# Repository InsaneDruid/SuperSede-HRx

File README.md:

# SuperSede-HRx - a HRx clone family
A 100% compatible replica of the HR40, HR40B &amp; HR80 graphics boards for the CBM PET lineup.

The SuperSede HRx are 100% compatible clones of the HR40, HR40B and HR80 graphics boards for the PET/CBM series computers from 1982, beginning with the dynamic board.
They implements all the features, including the high 320*200 pixel high resolution graphics that can be mixed standard text output on a per character base, the availability of the 8k of onboard RAM for Data usage and the possibility to use existing ROM expansion on the graphics board.

## The HR40 board for the non CRTC 40column dynamic PET lineup

[Schematic](https://github.com/InsaneDruid/SuperSede-HRx/blob/main/hr40/hr40.pdf "Schematic")  

[Bill of Materials](https://htmlpreview.github.io/?https://github.com/InsaneDruid/SuperSede-HRx/blob/main/hr40/bom/hr40_bom.html "Bill of Materials")

[Wire connections](https://github.com/InsaneDruid/SuperSede-HRx/blob/main/hr40/hr40_connections.pdf "Wire connections" )

* The connection to the Character ROM can be made with a standard DIP24 to ribbon cable adapter.

* The connection to UF8 can be made with the provided breakout adapter found in [adapter_uf8](https://github.com/InsaneDruid/SuperSede-HRx/blob/main/adapter_uf8/ "adapter_uf8").

## The HR40b board for the CRTC based 40column PET/CBM lineup

[Schematic](https://github.com/InsaneDruid/SuperSede-HRx/blob/main/hr40b/hr40b.pdf "Schematic")  

[Bill of Materials](https://htmlpreview.github.io/?https://github.com/InsaneDruid/SuperSede-HRx/blob/main/hr40b/bom/hr40b_bom.html "Bill of Materials")

[Wire connections](https://github.com/InsaneDruid/SuperSede-HRx/blob/main/hr40b/hr40b_connections.pdf "Wire connections" )

* The connection to the CRTC can be made with the provided breakout adapter found in [adapter_crtc](https://github.com/InsaneDruid/SuperSede-HRx/blob/main/adapter_crtc/ "adapter_crtc").

## The HR80 board for the 80column CBM lineup (8032, 8032SK*, 8096)

[Schematic](https://github.com/InsaneDruid/SuperSede-HRx/blob/main/hr80/hr80.pdf "Schematic")  

[Bill of Materials](https://htmlpreview.github.io/?https://github.com/InsaneDruid/SuperSede-HRx/blob/main/hr80/bom/hr80_bom.html "Bill of Materials")

[Wire connections](https://github.com/InsaneDruid/SuperSede-HRx/blob/main/hr80/hr80_connections.pdf "Wire connections" )

* The connection to the CRTC can be made with the provided breakout adapter found in [adapter_crtc](https://github.com/InsaneDruid/SuperSede-HRx/blob/main/adapter_crtc/ "adapter_crtc").

## The SuperSede cards and Expansion ROMs
The SuperSede boards hav 8k of their own RAM which occupies memory locations 36864 to 45055 ($9000 to $AFFF). This is the Rom Expansion area, normally represented by sockets UD11 and UD12 (UD3 and UD4 for 9-inch PETs). 

When you power-up your computer the ROM sockets are enabled and the high resolution memory disabled. Thus Rom expansions can be used in standard text mode like normal.

## The Firmware
The firmware needed for the SuperSede cards consist of

* A modified CharRom (with inverted characters).
* A 4k ROM containing the EditorROM followed by the GRAPHIX software in the E900-EFFF area.

The Firmware and supporting tools are available on their own repository: [SuperSede-HRx-Software](https://github.com/InsaneDruid/SuperSede-HRx-Software/ "Firmware and tools for the SuperSede HRx boards ")

## The License
This work is licensed under a Creative Commons Attribution-ShareAlike 4.0 International License.   
See https://creativecommons.org/licenses/by-sa/4.0/.

## The Credits
This work would not have been possible without the help from a bunch of amazing people from [VzEkC e. V. forums](https://forum.classic-computing.de/forum/ "forum.classic-computing.de"). Many thanks go out to:

* *Andy Grady* - for the scans of a blank board that formed the backbone for this project, the construction of the first prototypes as well as writing the print routines and assembling the firmware for the cards.
* *Steve Gray* - for collecting a ton of information about the cards
* *CBM_Ba* and *Richy* - for prototyping, testing, feedback and general positive retrocomputing craziness

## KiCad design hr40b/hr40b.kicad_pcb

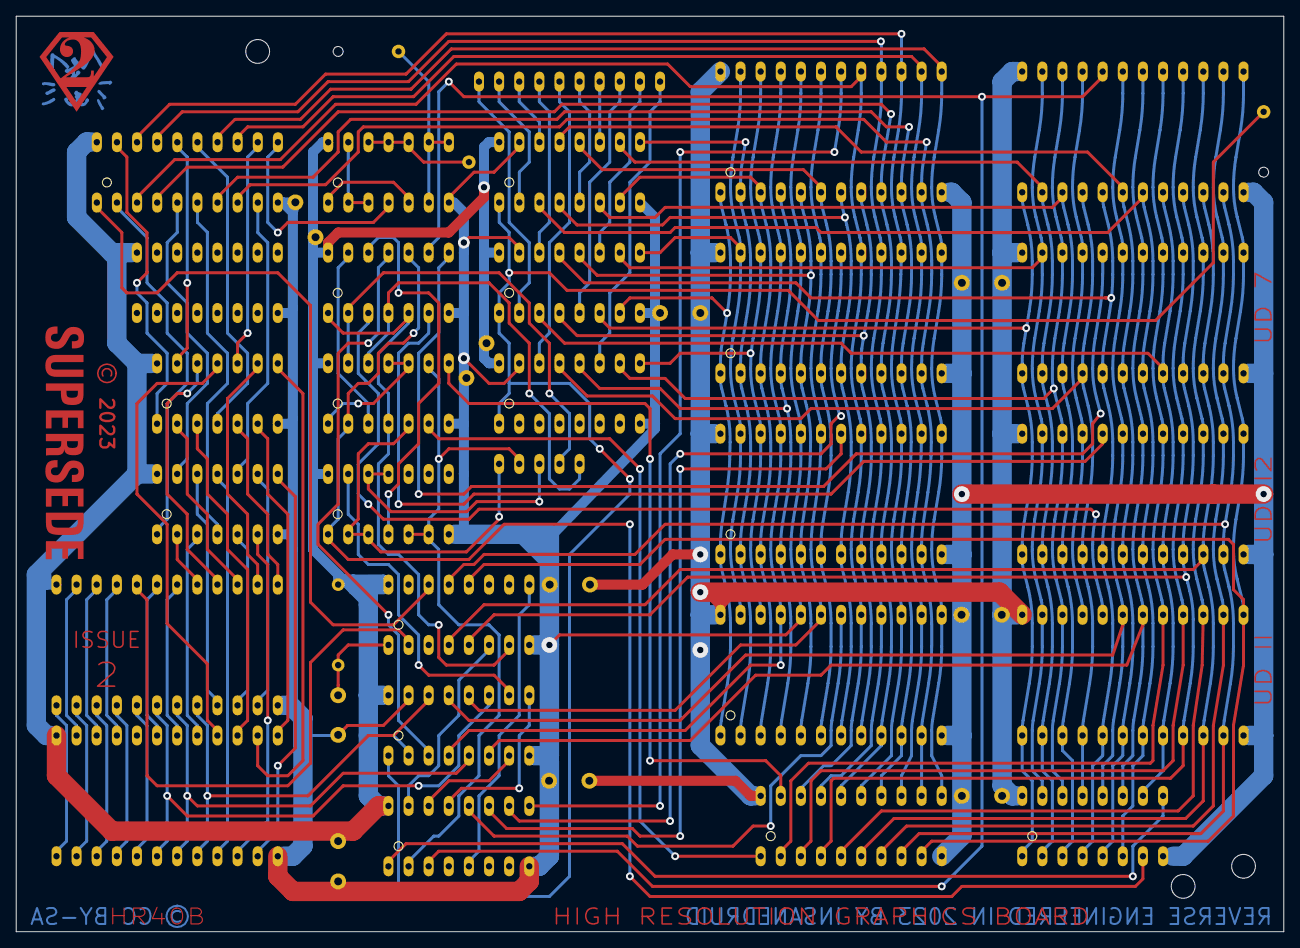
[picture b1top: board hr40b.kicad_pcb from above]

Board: 2 copper layers, 160.0 x 115.6 mm, 47 parts (0 on the bottom side), 128 nets.

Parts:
C1: 2.2uF; CP_Radial_D10.0mm_P5.00mm
C2, C3, C4, C5, C6, C7, C8, C9, C10: 100nF; C_Disc_D7.5mm_W2.5mm_P5.08mm
H1: CLK1; PinHeader_1x01_P2.54mm_Vertical
H2: VIDEO_LATCH; PinHeader_1x01_P2.54mm_Vertical
J0: charROM ADAPTER; DIP-24_W15.24mm_Adapter
J1: editorROM ADAPTER; DIP-24_W15.24mm_Adapter
J2: PET CRTC; PinHeader_1x10_P2.54mm_Vertical
J3: PET J4 / J9; PinHeader_1x05_P2.54mm_Vertical
MH0, MH5: MountingHole_3mm
MH2: MountingHole_1.25mm
Mh4: MountingHole_3mm
R1: 47k; R_Axial_DIN0207_L6.3mm_D2.5mm_P10.16mm_Horizontal
RMH1: MountingHole_1.25mm
TP1: MountingHole_Pad; PinHeader_1x01_P2.54mm_Vertical
U1: 74LS373; DIP-20_W7.62mm_LongPads
U2: 74LS157; DIP-16_W7.62mm_LongPads_Empty
U3, U4, U9: 74LS00; DIP-14_W7.62mm_LongPads
U5: 2316; DIP-24_W15.24mm_Socket_LongPads
U7, U10: 74LS02; DIP-14_W7.62mm_LongPads
U8: 74LS32; DIP-14_W7.62mm_LongPads
U11: 74LS175; DIP-16_W7.62mm_LongPads
U12, U14, U15, U16: 74LS157; DIP-16_W7.62mm_LongPads
U13: 74LS139; DIP-16_W7.62mm_LongPads
U17, U18, U19, U20: 6116; DIP-24_W15.24mm_LongPads
U21: 74LS245; DIP-20_W7.62mm_LongPads
U26: 74LS133; DIP-16_W7.62mm_LongPads
UD7: 2316; DIP-24_W15.24mm_Socket_LongPads
UD11, UD12: 2332A; DIP-24_W15.24mm_Socket_LongPads

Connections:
+5V: C2.1, C3.1, C4.1, J0.24 (VCC), R1.1, U1.20 (VCC), U2.16 (VCC), U3.14 (VCC), U4.14 (VCC), U5.24 (VCC), U7.14 (VCC), U8.14 (VCC), U9.14 (VCC), U10.14 (VCC), U11.16 (VCC), U12.2 (I0a), U12.16 (VCC), U13.16 (VCC), U14.16 (VCC), U15.16 (VCC), U16.16 (VCC)
+5VA: C5.1, C6.1, C7.1, C8.1, C9.1, C10.1, J1.24 (VCC), U17.24 (VCC), U18.24 (VCC), U19.24 (VCC), U20.24 (VCC), U21.20 (VCC), U26.16 (VCC), UD7.24 (VCC), UD11.24 (VCC), UD12.24 (VCC)
/A_{CHAR}0: J0.8 (A0), U5.8 (A0), U12.14 (I0d)
/A_{CHAR}1: J0.7 (A1), U5.7 (A1), U12.5 (I0b)
/A_{CHAR}2: J0.6 (A2), U5.6 (A2), U12.11 (I0c)
/A_{CHAR}3: J0.5 (A3), U5.5 (A3)
/A_{CHAR}4: J0.4 (A4), U5.4 (A4)
/A_{CHAR}5: J0.3 (A5), U5.3 (A5)
/A_{CHAR}6: J0.2 (A6), U5.2 (A6)
/A_{CHAR}7: J0.1 (A7), U5.1 (A7)
/A_{CHAR}8: J0.23 (A8), U5.23 (A8)
/A_{CHAR}9: J0.22 (A9), U5.22 (A9)
/A_{CHAR}10: J0.19 (A10), U5.19 (A10)
/A_{CHAR}11: J0.18 (~CS2), U5.18 (~CS2)
/A_{PET}0: J1.8 (A0), U15.3 (I1a), U26.10, UD7.8 (A0), UD11.8 (A0), UD12.8 (A0)
/A_{PET}1: J1.7 (A1), U14.3 (I1a), U26.6, UD7.7 (A1), UD11.7 (A1), UD12.7 (A1)
/A_{PET}2: J1.6 (A2), U14.13 (I1d), U26.5, UD7.6 (A2), UD11.6 (A2), UD12.6 (A2)
/A_{PET}3: J1.5 (A3), U15.13 (I1d), U26.4, UD7.5 (A3), UD11.5 (A3), UD12.5 (A3)
/A_{PET}4: J1.4 (A4), U16.13 (I1d), U26.13, UD7.4 (A4), UD11.4 (A4), UD12.4 (A4)
/A_{PET}5: J1.3 (A5), U14.6 (I1b), U26.3, UD7.3 (A5), UD11.3 (A5), UD12.3 (A5)
/A_{PET}6: J1.2 (A6), U14.10 (I1c), U26.2, UD7.2 (A6), UD11.2 (A6), UD12.2 (A6)
/A_{PET}7: J1.1 (A7), U15.6 (I1b), U26.1, UD7.1 (A7), UD11.1 (A7), UD12.1 (A7)
/A_{PET}8: J1.23 (A8), U15.10 (I1c), U26.15, UD7.23 (A8), UD11.23 (A8), UD12.23 (A8)
/A_{PET}9: J1.22 (A9), U16.10 (I1c), U26.14, UD7.22 (A9), UD11.22 (A9), UD12.22 (A9)
/A_{RAM}0: U15.4 (Za), U17.8 (A0), U18.8 (A0), U19.8 (A0), U20.8 (A0)
/A_{RAM}1: U14.4 (Za), U17.7 (A1), U18.7 (A1), U19.7 (A1), U20.7 (A1)
/A_{RAM}2: U14.12 (Zd), U17.6 (A2), U18.6 (A2), U19.6 (A2), U20.6 (A2)
/A_{RAM}3: U15.12 (Zd), U17.5 (A3), U18.5 (A3), U19.5 (A3), U20.5 (A3)
/A_{RAM}4: U16.12 (Zd), U17.4 (A4), U18.4 (A4), U19.4 (A4), U20.4 (A4)
/A_{RAM}5: U14.7 (Zb), U17.3 (A5), U18.3 (A5), U19.3 (A5), U20.3 (A5)
/A_{RAM}6: U14.9 (Zc), U17.2 (A6), U18.2 (A6), U19.2 (A6), U20.2 (A6)
/A_{RAM}7: U15.7 (Zb), U17.1 (A7), U18.1 (A7), U19.1 (A7), U20.1 (A7)
/A_{RAM}8: U15.9 (Zc), U17.23 (A8), U18.23 (A8), U19.23 (A8), U20.23 (A8)
/A_{RAM}9: U16.9 (Zc), U17.22 (A9), U18.22 (A9), U19.22 (A9), U20.22 (A9)
/A_{RAM}10: U12.12 (Zd), U17.19 (A10), U18.19 (A10), U19.19 (A10), U20.19 (A10)
/BA12: J3.3, U10.11, U10.12
/BR/W: J3.1, U9.5, U10.2, U10.3
/CS1_{PET}: J1.21 (~CS3), UD7.21 (~CS3), UD11.21 (CS1), UD12.21 (CS1)
/D_{CHAR}0: U4.12, U5.9 (D0)
/D_{CHAR}1: U4.5, U5.10 (D1)
/D_{CHAR}2: U4.9, U5.11 (D2)
/D_{CHAR}3: U3.5, U5.13 (D3)
/D_{CHAR}4: U3.9, U5.14 (D4)
/D_{CHAR}5: U3.2, U5.15 (D5)
/D_{CHAR}6: U3.12, U5.16 (D6)
/D_{CHAR}7: U4.2, U5.17 (D7)
/D_{OUT}0: U1.5 (O1), U4.13
/D_{OUT}1: U1.6 (O2), U4.4
/D_{OUT}2: U1.9 (O3), U4.10
/D_{OUT}3: U1.15 (O5), U3.4
/D_{OUT}4: U1.12 (O4), U3.10
/D_{OUT}5: U1.19 (O7), U3.1
/D_{OUT}6: U1.16 (O6), U3.13
/D_{OUT}7: U1.2 (O0), U4.1
/D_{PET}0: J1.9 (D0), U11.5 (D1), U21.4 (A2), UD7.9 (D0), UD11.9 (D0), UD12.9 (D0)
/D_{PET}1: J1.10 (D1), U11.4 (D0), U21.6 (A4), UD7.10 (D1), UD11.10 (D1), UD12.10 (D1)
/D_{PET}2: J1.11 (D2), U11.13 (D3), U21.8 (A6), UD7.11 (D2), UD11.11 (D2), UD12.11 (D2)
/D_{PET}3: J1.13 (D3), U11.12 (D2), U21.9 (A7), UD7.13 (D3), UD11.13 (D3), UD12.13 (D3)
/D_{PET}4: J1.14 (D4), U21.7 (A5), UD7.14 (D4), UD11.14 (D4), UD12.14 (D4)
/D_{PET}5: J1.15 (D5), U21.5 (A3), UD7.15 (D5), UD11.15 (D5), UD12.15 (D5)
/D_{PET}6: J1.16 (D6), U21.3 (A1), UD7.16 (D6), UD11.16 (D6), UD12.16 (D6)
/D_{PET}7: J1.17 (D7), U21.2 (A0), UD7.17 (D7), UD11.17 (D7), UD12.17 (D7)
/D_{RAM}0: U1.4 (D1), U17.9 (D0), U18.9 (D0), U19.9 (D0), U20.9 (D0), U21.16 (B2)
/D_{RAM}1: U1.7 (D2), U17.10 (D1), U18.10 (D1), U19.10 (D1), U20.10 (D1), U21.14 (B4)
/D_{RAM}2: U1.8 (D3), U17.11 (D2), U18.11 (D2), U19.11 (D2), U20.11 (D2), U21.12 (B6)
/D_{RAM}3: U1.14 (D5), U17.13 (D3), U18.13 (D3), U19.13 (D3), U20.13 (D3), U21.11 (B7)
/D_{RAM}4: U1.13 (D4), U17.14 (D4), U18.14 (D4), U19.14 (D4), U20.14 (D4), U21.13 (B5)
/D_{RAM}5: U1.18 (D7), U17.15 (D5), U18.15 (D5), U19.15 (D5), U20.15 (D5), U21.15 (B3)
/D_{RAM}6: U1.17 (D6), U17.16 (D6), U18.16 (D6), U19.16 (D6), U20.16 (D6), U21.17 (B1)
/D_{RAM}7: U1.3 (D0), U17.17 (D7), U18.17 (D7), U19.17 (D7), U20.17 (D7), U21.18 (B0)
/D_{VIDEO}0: J0.9 (D0), U4.11
/D_{VIDEO}1: J0.10 (D1), U4.6
/D_{VIDEO}2: J0.11 (D2), U4.8
/D_{VIDEO}3: J0.13 (D3), U3.6
/D_{VIDEO}4: J0.14 (D4), U3.8
/D_{VIDEO}5: J0.15 (D5), U3.3
/D_{VIDEO}6: J0.16 (D6), U3.11
/D_{VIDEO}7: J0.17 (D7), U4.3
/PHI2: J3.2, U9.9, U10.5, U10.6, U13.2 (A0)
/PULSE_VIDEO_LATCH: U1.11 (LE), U7.4
/TA0: J2.1, U15.2 (I0a)
/TA1: J2.2, U14.2 (I0a)
/TA2: J2.3, U14.14 (I0d)
/TA3: J2.4, U15.14 (I0d)
/TA4: J2.5, U16.14 (I0d)
/TA5: J2.6, U14.5 (I0b)
/TA6: J2.7, U14.11 (I0c)
/TA7: J2.8, U15.5 (I0b)
/TA8: J2.9, U15.11 (I0c)
/TA9: J2.10, U16.11 (I0c)
/VIDEO_LATCH: H2.1, U7.6, U7.8, U7.9
/~CS3_{CHAR}: J0.21 (~CS3), U5.21 (~CS3)
/~SEL9: J3.5, U8.4, U9.12
/~SELA: J3.4, U8.2, U9.13
/~WE: U8.11, U12.3 (I1a)
A_{PET}10: J1.19 (A10), U12.13 (I1d), U26.12, UD7.19 (A10), UD11.19 (A10), UD12.19 (A10)
A_{PET}11: J1.18 (~CS2), U12.6 (I1b), U26.11, UD7.18 (~CS2), UD11.18 (A11), UD12.18 (A11)
CLK1: H1.1, U12.1 (S), U14.1 (S), U15.1 (S), U16.1 (S)
CS_{PETtoRAM}: U9.8, U21.19 (CE)
GND: C1.2, C2.2, C3.2, C4.2, C5.2, C6.2, C7.2, J0.12 (GND), U1.10 (GND), U2.8 (GND), U3.7 (GND), U4.7 (GND), U5.12 (GND), U7.7 (GND), U8.7 (GND), U9.7 (GND), U10.7 (GND), U11.8 (GND), U12.8 (GND), U12.15 (E), U13.8 (GND), U14.8 (GND), U14.15 (E), U15.8 (GND), U15.15 (E), U16.8 (GND), U16.15 (E), U17.20 (~OE), U18.20 (~OE), U19.20 (~OE), U20.20 (~OE)
GNDA: C8.2, C9.2, C10.2, J1.12 (GND), U17.12 (GND), U18.12 (GND), U19.12 (GND), U20.12 (GND), U21.10 (GND), U26.8 (GND), UD7.12 (GND), UD11.12 (GND), UD12.12 (GND)
unnamed: TP1.1, U7.10, U7.11, U7.12
unnamed: U7.1, U7.5
unnamed: U7.2, U7.3, U7.13
unnamed: U9.1, U9.10, U9.11
unnamed: U11.9 (Cp), U13.5 (O1)
unnamed: U8.1, U8.5, U9.4, U11.7 (Q1)
unnamed: C1.1, R1.2, U11.1 (~Mr)
unnamed: U11.6 (~Q1), U13.15 (E)
unnamed: U10.13, U12.10 (I1c)
unnamed: U12.7 (Zb), U13.14 (A0)
unnamed: U12.9 (Zc), U13.13 (A1)
OE_{LATCH_RAM}: U1.1 (OE), U11.14 (~Q3)
SWITCH_{PETtoRAM}: U9.6, U21.1 (A->B)
WEa: U8.12, U10.4
WEb: U8.13, U9.3
~ADDR: U13.1 (E), U26.9
~BR_W: U8.10, U9.2, U10.1, U26.7
~CS1_CHAR: U5.20 (~CS1), U11.2 (Q0)
~CS_{RAM1}: U13.9 (O3), U17.18 (~CS)
~CS_{RAM2}: U13.10 (O2), U18.18 (~CS)
~CS_{RAM3}: U13.11 (O1), U19.18 (~CS)
~CS_{RAM4}: U13.12 (O0), U20.18 (~CS)
~SEL9_{A}: U8.6, UD12.20 (~CS2)
~SELA_{A}: U8.3, UD11.20 (~CS2)
~SELE: J1.20 (~CS1), U8.9, U13.3 (A1)
~SELE_{A}: U8.8, UD7.20 (~CS1)
~WE_{RAM}: U12.4 (Za), U17.21 (~WE), U18.21 (~WE), U19.21 (~WE), U20.21 (~WE)

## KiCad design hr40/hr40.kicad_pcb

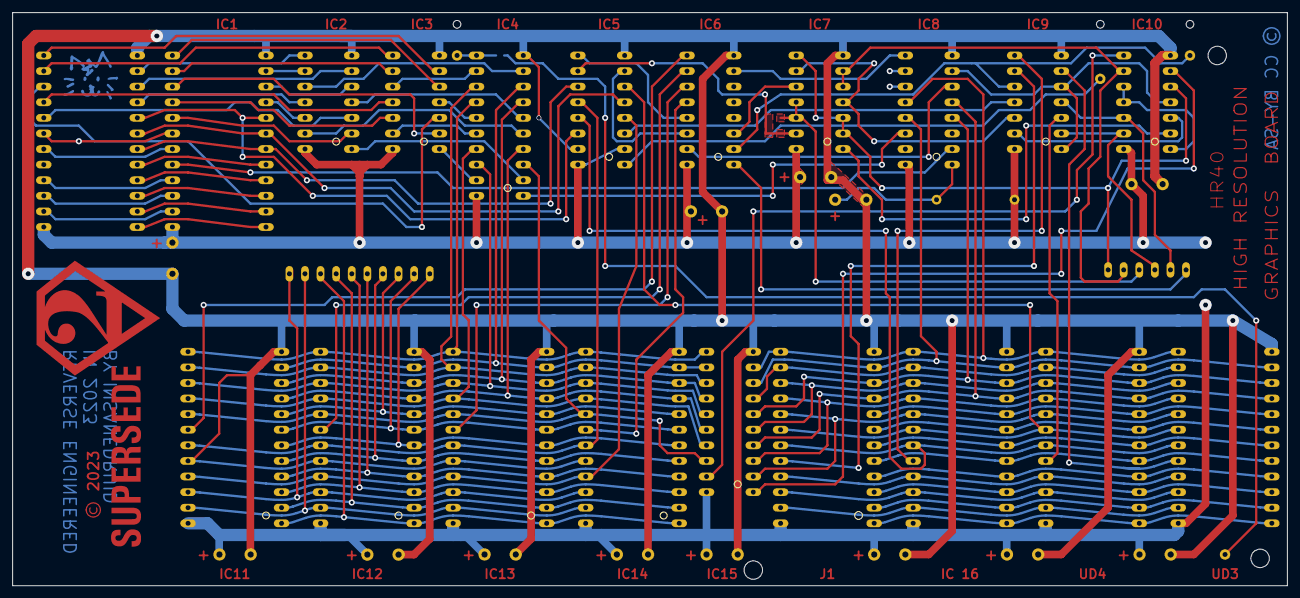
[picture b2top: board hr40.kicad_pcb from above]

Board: 2 copper layers, 207.6 x 93.3 mm, 47 parts (1 on the bottom side), 116 nets.

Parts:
C2, C3, C4, C5, C6, C7, C9, C10, C11, C12, C13, C14: 100nF; C_Disc_D7.5mm_W2.5mm_P5.08mm
C8: 2.2uF; C_Disc_D7.5mm_W2.5mm_P5.08mm
H1: CLK1; PinHeader_1x01_P2.54mm_Vertical
H2, H4: VIDEO_LATCH; PinHeader_1x01_P2.54mm_Vertical
H3: X8XX; PinHeader_1x01_P2.54mm_Vertical
IC1: 2316; DIP-24_W15.24mm_Socket_LongPads
IC2, IC3, IC10: 74LS00; DIP-14_W7.62mm_LongPads
IC4: 74LS373; DIP-20_W7.62mm_LongPads
IC5: 74LS157; DIP-16_W7.62mm_LongPads
IC6: 74LS139; DIP-16_W7.62mm_LongPads
IC7: 74LS02; DIP-14_W7.62mm_LongPads
IC8: 74LS175; DIP-16_W7.62mm_LongPads
IC9: 74LS32; DIP-14_W7.62mm_LongPads
IC11, IC12, IC13, IC14: 6116; DIP-24_W15.24mm_LongPads
IC16: 2332A; DIP-24_W15.24mm_Socket_LongPads
J0: charROM ADAPTER; DIP-24_W15.24mm_Adapter
J1: editorROM ADAPTER; DIP-24_W15.24mm_WireAdapter
J2: PET F8; PinHeader_1x10_P2.54mm_Vertical
J3: PET J4 / J9; PinHeader_1x06_P2.54mm_Vertical
JP1: Jumper_2_Open; SolderJumper-2_P1.3mm_Open_RoundedPad1.0x1.5mm
MH0, MH1, MH2: MountingHole_1.25mm
MH3, MH4, MH5: MountingHole_3mm
R1: 47k; R_Axial_DIN0207_L6.3mm_D2.5mm_P12.70mm_Horizontal
U21: 74LS245; DIP-20_W7.62mm_LongPads
UD3, UD4: 2332A; DIP-24_W15.24mm_Socket_LongPads

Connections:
+5V: C2.1, C4.1, C6.1, C7.1, IC1.24 (VCC), IC2.14 (VCC), IC3.14 (VCC), IC4.20 (VCC), IC5.2 (I0a), IC5.16 (VCC), IC6.16 (VCC), IC7.14 (VCC), IC8.16 (VCC), IC9.14 (VCC), IC10.14 (VCC), J0.24 (VCC), R1.1
+5VA: C3.1, C5.1, C9.1, C10.1, C11.1, C12.1, C13.1, C14.1, IC11.24 (VCC), IC12.24 (VCC), IC13.24 (VCC), IC14.24 (VCC), IC16.24 (VCC), J1.24 (VCC), U21.20 (VCC), UD3.24 (VCC), UD4.24 (VCC)
/A_{CHAR}0: IC1.8 (A0), IC5.14 (I0d), J0.8 (A0)
/A_{CHAR}1: IC1.7 (A1), IC5.5 (I0b), J0.7 (A1)
/A_{CHAR}2: IC1.6 (A2), IC5.11 (I0c), J0.6 (A2)
/A_{CHAR}3: IC1.5 (A3), J0.5 (A3)
/A_{CHAR}4: IC1.4 (A4), J0.4 (A4)
/A_{CHAR}5: IC1.3 (A5), J0.3 (A5)
/A_{CHAR}6: IC1.2 (A6), J0.2 (A6)
/A_{CHAR}7: IC1.1 (A7), J0.1 (A7)
/A_{CHAR}8: IC1.23 (A8), J0.23 (A8)
/A_{CHAR}9: IC1.22 (A9), J0.22 (A9)
/A_{CHAR}10: IC1.19 (A10), J0.19 (A10)
/A_{CHAR}11: IC1.18 (~CS2), J0.18 (~CS2)
/A_{PET}0: IC16.8 (A0), J1.8 (A0), UD3.8 (A0), UD4.8 (A0)
/A_{PET}1: IC16.7 (A1), J1.7 (A1), UD3.7 (A1), UD4.7 (A1)
/A_{PET}2: IC16.6 (A2), J1.6 (A2), UD3.6 (A2), UD4.6 (A2)
/A_{PET}3: IC16.5 (A3), J1.5 (A3), UD3.5 (A3), UD4.5 (A3)
/A_{PET}4: IC16.4 (A4), J1.4 (A4), UD3.4 (A4), UD4.4 (A4)
/A_{PET}5: IC16.3 (A5), J1.3 (A5), UD3.3 (A5), UD4.3 (A5)
/A_{PET}6: IC16.2 (A6), J1.2 (A6), UD3.2 (A6), UD4.2 (A6)
/A_{PET}7: IC16.1 (A7), J1.1 (A7), UD3.1 (A7), UD4.1 (A7)
/A_{PET}8: IC16.23 (A8), J1.23 (A8), UD3.23 (A8), UD4.23 (A8)
/A_{PET}9: IC16.22 (A9), J1.22 (A9), UD3.22 (A9), UD4.22 (A9)
/A_{RAM}0: IC11.8 (A0), IC12.8 (A0), IC13.8 (A0), IC14.8 (A0), J2.8
/A_{RAM}1: IC11.7 (A1), IC12.7 (A1), IC13.7 (A1), IC14.7 (A1), J2.9
/A_{RAM}2: IC11.6 (A2), IC12.6 (A2), IC13.6 (A2), IC14.6 (A2), J2.10
/A_{RAM}3: IC11.5 (A3), IC12.5 (A3), IC13.5 (A3), IC14.5 (A3), J2.7
/A_{RAM}4: IC11.4 (A4), IC12.4 (A4), IC13.4 (A4), IC14.4 (A4), J2.6
/A_{RAM}5: IC11.3 (A5), IC12.3 (A5), IC13.3 (A5), IC14.3 (A5), J2.5
/A_{RAM}6: IC11.2 (A6), IC12.2 (A6), IC13.2 (A6), IC14.2 (A6), J2.4
/A_{RAM}7: IC11.1 (A7), IC12.1 (A7), IC13.1 (A7), IC14.1 (A7), J2.3
/A_{RAM}8: IC11.23 (A8), IC12.23 (A8), IC13.23 (A8), IC14.23 (A8), J2.2
/A_{RAM}9: IC11.22 (A9), IC12.22 (A9), IC13.22 (A9), IC14.22 (A9), J2.1
/A_{RAM}10: IC5.12 (Zd), IC11.19 (A10), IC12.19 (A10), IC13.19 (A10), IC14.19 (A10)
/BA12: IC7.11, IC7.12, J3.3
/BR/W: IC7.2, IC7.3, IC7.8, IC10.5, J3.1
/CS1_{PET}: IC16.21 (CS1), J1.21 (CS1), UD3.21 (CS1), UD4.21 (CS1)
/D_{CHAR}0: IC1.9 (D0), IC3.12
/D_{CHAR}1: IC1.10 (D1), IC3.5
/D_{CHAR}2: IC1.11 (D2), IC3.9
/D_{CHAR}3: IC1.13 (D3), IC2.5
/D_{CHAR}4: IC1.14 (D4), IC2.9
/D_{CHAR}5: IC1.15 (D5), IC2.2
/D_{CHAR}6: IC1.16 (D6), IC2.12
/D_{CHAR}7: IC1.17 (D7), IC3.2
/D_{OUT}0: IC3.13, IC4.5 (O1)
/D_{OUT}1: IC3.4, IC4.6 (O2)
/D_{OUT}2: IC3.10, IC4.9 (O3)
/D_{OUT}3: IC2.4, IC4.15 (O5)
/D_{OUT}4: IC2.10, IC4.12 (O4)
/D_{OUT}5: IC2.1, IC4.19 (O7)
/D_{OUT}6: IC2.13, IC4.16 (O6)
/D_{OUT}7: IC3.1, IC4.2 (O0)
/D_{PET}0: IC8.5 (D1), IC16.9 (D0), J1.9 (D0), U21.4 (A2), UD3.9 (D0), UD4.9 (D0)
/D_{PET}1: IC8.4 (D0), IC16.10 (D1), J1.10 (D1), U21.6 (A4), UD3.10 (D1), UD4.10 (D1)
/D_{PET}2: IC8.13 (D3), IC16.11 (D2), J1.11 (D2), U21.8 (A6), UD3.11 (D2), UD4.11 (D2)
/D_{PET}3: IC8.12 (D2), IC16.13 (D3), J1.13 (D3), U21.9 (A7), UD3.13 (D3), UD4.13 (D3)
/D_{PET}4: IC16.14 (D4), J1.14 (D4), U21.7 (A5), UD3.14 (D4), UD4.14 (D4)
/D_{PET}5: IC16.15 (D5), J1.15 (D5), U21.5 (A3), UD3.15 (D5), UD4.15 (D5)
/D_{PET}6: IC16.16 (D6), J1.16 (D6), U21.3 (A1), UD3.16 (D6), UD4.16 (D6)
/D_{PET}7: IC16.17 (D7), J1.17 (D7), U21.2 (A0), UD3.17 (D7), UD4.17 (D7)
/D_{RAM}0: IC4.4 (D1), IC11.9 (D0), IC12.9 (D0), IC13.9 (D0), IC14.9 (D0), U21.16 (B2)
/D_{RAM}1: IC4.7 (D2), IC11.10 (D1), IC12.10 (D1), IC13.10 (D1), IC14.10 (D1), U21.14 (B4)
/D_{RAM}2: IC4.8 (D3), IC11.11 (D2), IC12.11 (D2), IC13.11 (D2), IC14.11 (D2), U21.12 (B6)
/D_{RAM}3: IC4.14 (D5), IC11.13 (D3), IC12.13 (D3), IC13.13 (D3), IC14.13 (D3), U21.11 (B7)
/D_{RAM}4: IC4.13 (D4), IC11.14 (D4), IC12.14 (D4), IC13.14 (D4), IC14.14 (D4), U21.13 (B5)
/D_{RAM}5: IC4.18 (D7), IC11.15 (D5), IC12.15 (D5), IC13.15 (D5), IC14.15 (D5), U21.15 (B3)
/D_{RAM}6: IC4.17 (D6), IC11.16 (D6), IC12.16 (D6), IC13.16 (D6), IC14.16 (D6), U21.17 (B1)
/D_{RAM}7: IC4.3 (D0), IC11.17 (D7), IC12.17 (D7), IC13.17 (D7), IC14.17 (D7), U21.18 (B0)
/D_{VIDEO}0: IC3.11, J0.9 (D0)
/D_{VIDEO}1: IC3.6, J0.10 (D1)
/D_{VIDEO}2: IC3.8, J0.11 (D2)
/D_{VIDEO}3: IC2.6, J0.13 (D3)
/D_{VIDEO}4: IC2.8, J0.14 (D4)
/D_{VIDEO}5: IC2.3, J0.15 (D5)
/D_{VIDEO}6: IC2.11, J0.16 (D6)
/D_{VIDEO}7: IC3.3, J0.17 (D7)
/PHI2: IC7.5, IC7.6, IC10.9, J3.2
/VIDEO_LATCH: H2.1, IC4.11 (LE), JP1.2 (B)
/X8XX: H3.1, IC6.2 (A0), IC9.10
/~BR/W: IC7.1, IC10.2
/~CS3_{CHAR}: IC1.21 (~CS3), J0.21 (~CS3)
/~SEL8: IC6.1 (E), J3.6
/~SEL9: IC9.4, IC10.12, J3.5
/~SELA: IC9.2, IC10.13, J3.4
/~WE: IC5.3 (I1a), IC9.11
A_{PET}10: IC5.13 (I1d), IC16.19 (A10), J1.19 (A10), UD3.19 (A10), UD4.19 (A10)
A_{PET}11: IC5.6 (I1b), IC16.18 (A11), J1.18 (A11), UD3.18 (A11), UD4.18 (A11)
CLK1: H1.1, IC5.1 (S)
CS_{PETtoRAM}: IC10.8, U21.19 (CE)
GND: C2.2, C3.2, C4.2, C5.2, C6.2, C7.2, C8.2, C9.2, C10.2, C11.2, C12.2, C13.2, C14.2, IC1.12 (GND), IC2.7 (GND), IC3.7 (GND), IC4.10 (GND), IC5.8 (GND), IC5.15 (E), IC6.8 (GND), IC7.7 (GND), IC8.8 (GND), IC9.7 (GND), IC10.7 (GND), IC11.12 (GND), IC11.20 (~OE), IC12.12 (GND), IC12.20 (~OE), IC13.12 (GND), IC13.20 (~OE), IC14.12 (GND), IC14.20 (~OE), IC16.12 (GND), J0.12 (GND), J1.12 (GND), U21.10 (GND), UD3.12 (GND), UD4.12 (GND)
unnamed: IC5.10 (I1c), IC7.13
unnamed: IC5.7 (Zb), IC6.14 (A0)
unnamed: IC5.9 (Zc), IC6.13 (A1)
unnamed: IC6.3 (A1), IC7.10
unnamed: IC6.7 (O3), IC8.9 (Cp)
unnamed: IC6.15 (E), IC8.6 (~Q1)
unnamed: IC8.7 (Q1), IC9.1, IC9.5, IC10.4
unnamed: C8.1, IC8.1 (~Mr), R1.2
unnamed: IC10.1, IC10.10, IC10.11
unnamed: H4.1, JP1.1 (A)
OE_{LATCH_RAM}: IC4.1 (OE), IC8.14 (~Q3)
SWITCH_{PETtoRAM}: IC10.6, U21.1 (A->B)
WEa: IC7.4, IC7.9, IC9.12
WEb: IC9.13, IC10.3
~CS1_CHAR: IC1.20 (~CS1), IC8.2 (Q0)
~CS_{RAM1}: IC6.9 (O3), IC11.18 (~CS)
~CS_{RAM2}: IC6.10 (O2), IC12.18 (~CS)
~CS_{RAM3}: IC6.11 (O1), IC13.18 (~CS)
~CS_{RAM4}: IC6.12 (O0), IC14.18 (~CS)
~SEL9_{A}: IC9.6, UD3.20 (~CS2)
~SELA_{A}: IC9.3, UD4.20 (~CS2)
~SELE: IC9.9, J1.20 (~CS2)
~SELE_{A}: IC9.8, IC16.20 (~CS2)
~WE_{RAM}: IC5.4 (Za), IC11.21 (~WE), IC12.21 (~WE), IC13.21 (~WE), IC14.21 (~WE)

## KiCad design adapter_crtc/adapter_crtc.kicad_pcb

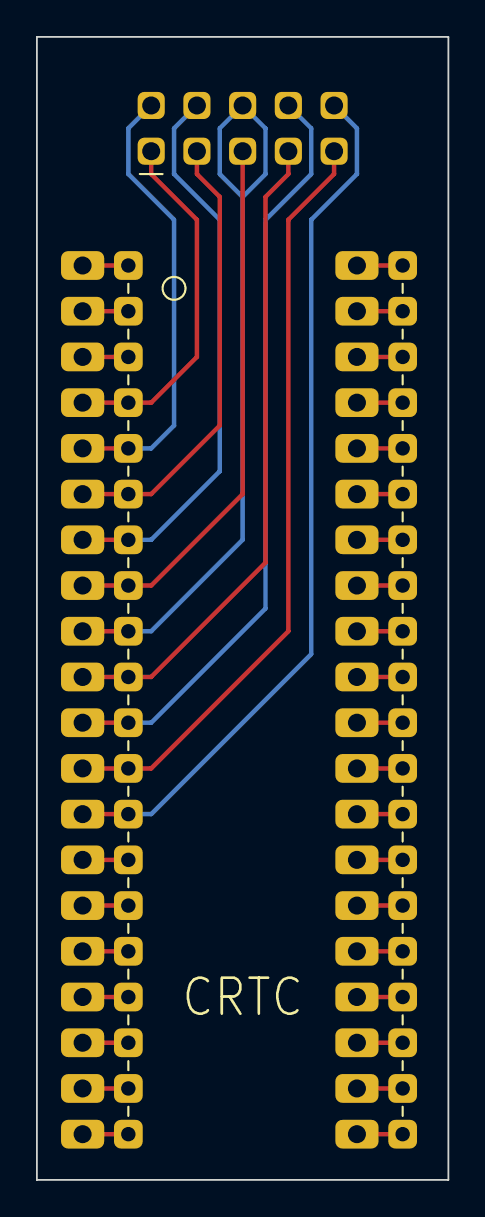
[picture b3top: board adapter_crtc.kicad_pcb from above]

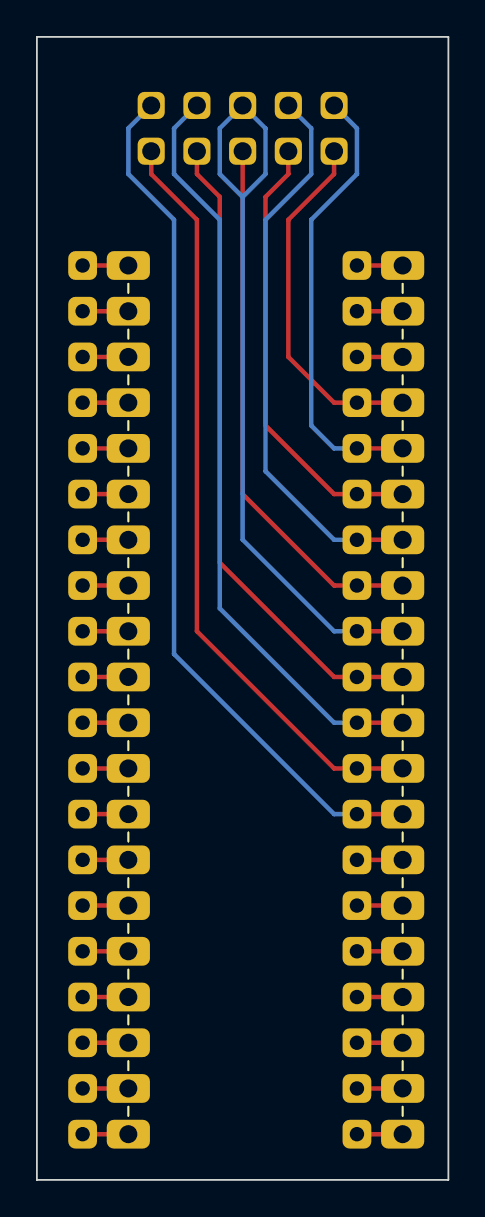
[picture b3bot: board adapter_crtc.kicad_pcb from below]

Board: 2 copper layers, 22.9 x 63.5 mm, 4 parts (2 on the bottom side), 40 nets.

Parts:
J1, J2: Conn_01x20_Male; PinHeader_1x20_P2.54mm_Vertical
J3: Conn_01x10_Male; Conn_02_05_Odd_Even
U1: 6545; DIP-40_W15.24mm_Socket

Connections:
+5V: J1.20, U1.20 (VCC)
/CCLOCK: J2.20, U1.21 (CCLK)
/CURSOR: J1.19, U1.19 (CURSOR)
/DB0: J2.8, U1.33 (DB0)
/DB1: J2.9, U1.32 (DB1)
/DB2: J2.10, U1.31 (DB2)
/DB3: J2.11, U1.30 (DB3)
/DB4: J2.12, U1.29 (DB4)
/DB5: J2.13, U1.28 (DB5)
/DB6: J2.14, U1.27 (DB6)
/DB7: J2.15, U1.26 (DB7)
/DISP_EN: J1.18, U1.18 (DISPLAY_ENABLE)
/HSYNC: J2.2, U1.39 (HSYNC)
/LPEN: J1.3, U1.3 (LPEN)
/MA0: J1.4, J3.1, U1.4 (MA0)
/MA1: J1.5, J3.2, U1.5 (MA1)
/MA2: J1.6, J3.3, U1.6 (MA2)
/MA3: J1.7, J3.4, U1.7 (MA3)
/MA4: J1.8, J3.5, U1.8 (MA4)
/MA5: J1.9, J3.6, U1.9 (MA5)
/MA6: J1.10, J3.7, U1.10 (MA6)
/MA7: J1.11, J3.8, U1.11 (MA7)
/MA8: J1.12, J3.9, U1.12 (MA8)
/MA9: J1.13, J3.10, U1.13 (MA9)
/MA10: J1.14, U1.14 (MA10)
/MA11: J1.15, U1.15 (MA11)
/MA12: J1.16, U1.16 (MA12)
/MA13: J1.17, U1.17 (MA13)
/PHI2: J2.18, U1.23 (PHI2)
/RA0: J2.3, U1.38 (RA0)
/RA1: J2.4, U1.37 (RA1)
/RA2: J2.5, U1.36 (RA2)
/RA3: J2.6, U1.35 (RA3)
/RA4: J2.7, U1.34 (RA4)
/RS: J2.17, U1.24 (RS)
/R/~W: J2.19, U1.22 (R/~W)
/VSYNC: J2.1, U1.40 (VSYNC)
/~CS: J2.16, U1.25 (~CS)
/~RES: J1.2, U1.2 (~RES)
GND: J1.1, U1.1 (GND)

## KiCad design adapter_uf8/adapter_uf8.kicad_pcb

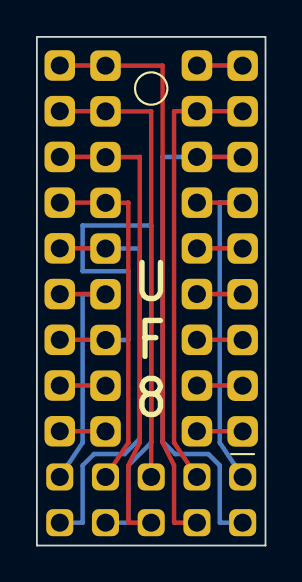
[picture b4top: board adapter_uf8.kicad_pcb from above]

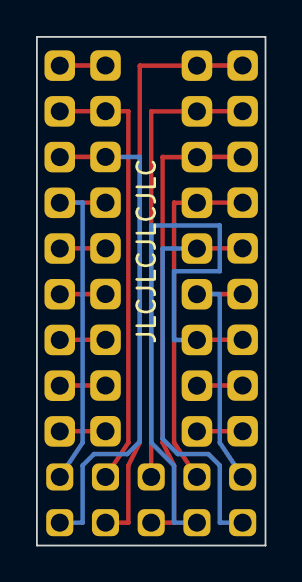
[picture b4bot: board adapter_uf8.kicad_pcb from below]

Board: 2 copper layers, 12.7 x 28.3 mm, 4 parts (2 on the bottom side), 18 nets.

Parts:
J1, J2: Conn_01x09_Male; PinHeader_1x09_P2.54mm_Vertical
J3: Conn_01x10_Male; Solderpad_02_05_Odd_Even
U1: 6114; DIP-18_W7.62mm_Socket

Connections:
+5V: J2.1, U1.18 (VCC)
/A0: J1.5, J3.10, U1.5 (A0)
/A1: J1.6, J3.9, U1.6 (A1)
/A2: J1.7, J3.8, U1.7 (A2)
/A3: J1.4, J3.7, U1.4 (A3)
/A4: J1.3, J3.6, U1.3 (A4)
/A5: J1.2, J3.5, U1.2 (A5)
/A6: J1.1, J3.4, U1.1 (A6)
/A7: J2.2, J3.3, U1.17 (A7)
/A8: J2.3, J3.2, U1.16 (A8)
/A9: J2.4, J3.1, U1.15 (A9)
/D0: J2.5, U1.14 (D0)
/D1: J2.6, U1.13 (D1)
/D2: J2.7, U1.12 (D2)
/D3: J2.8, U1.11 (D3)
/R~W: J2.9, U1.10 (R/~W)
/~CS: J1.8, U1.8 (~CS)
GND: J1.9, U1.9 (VSS)

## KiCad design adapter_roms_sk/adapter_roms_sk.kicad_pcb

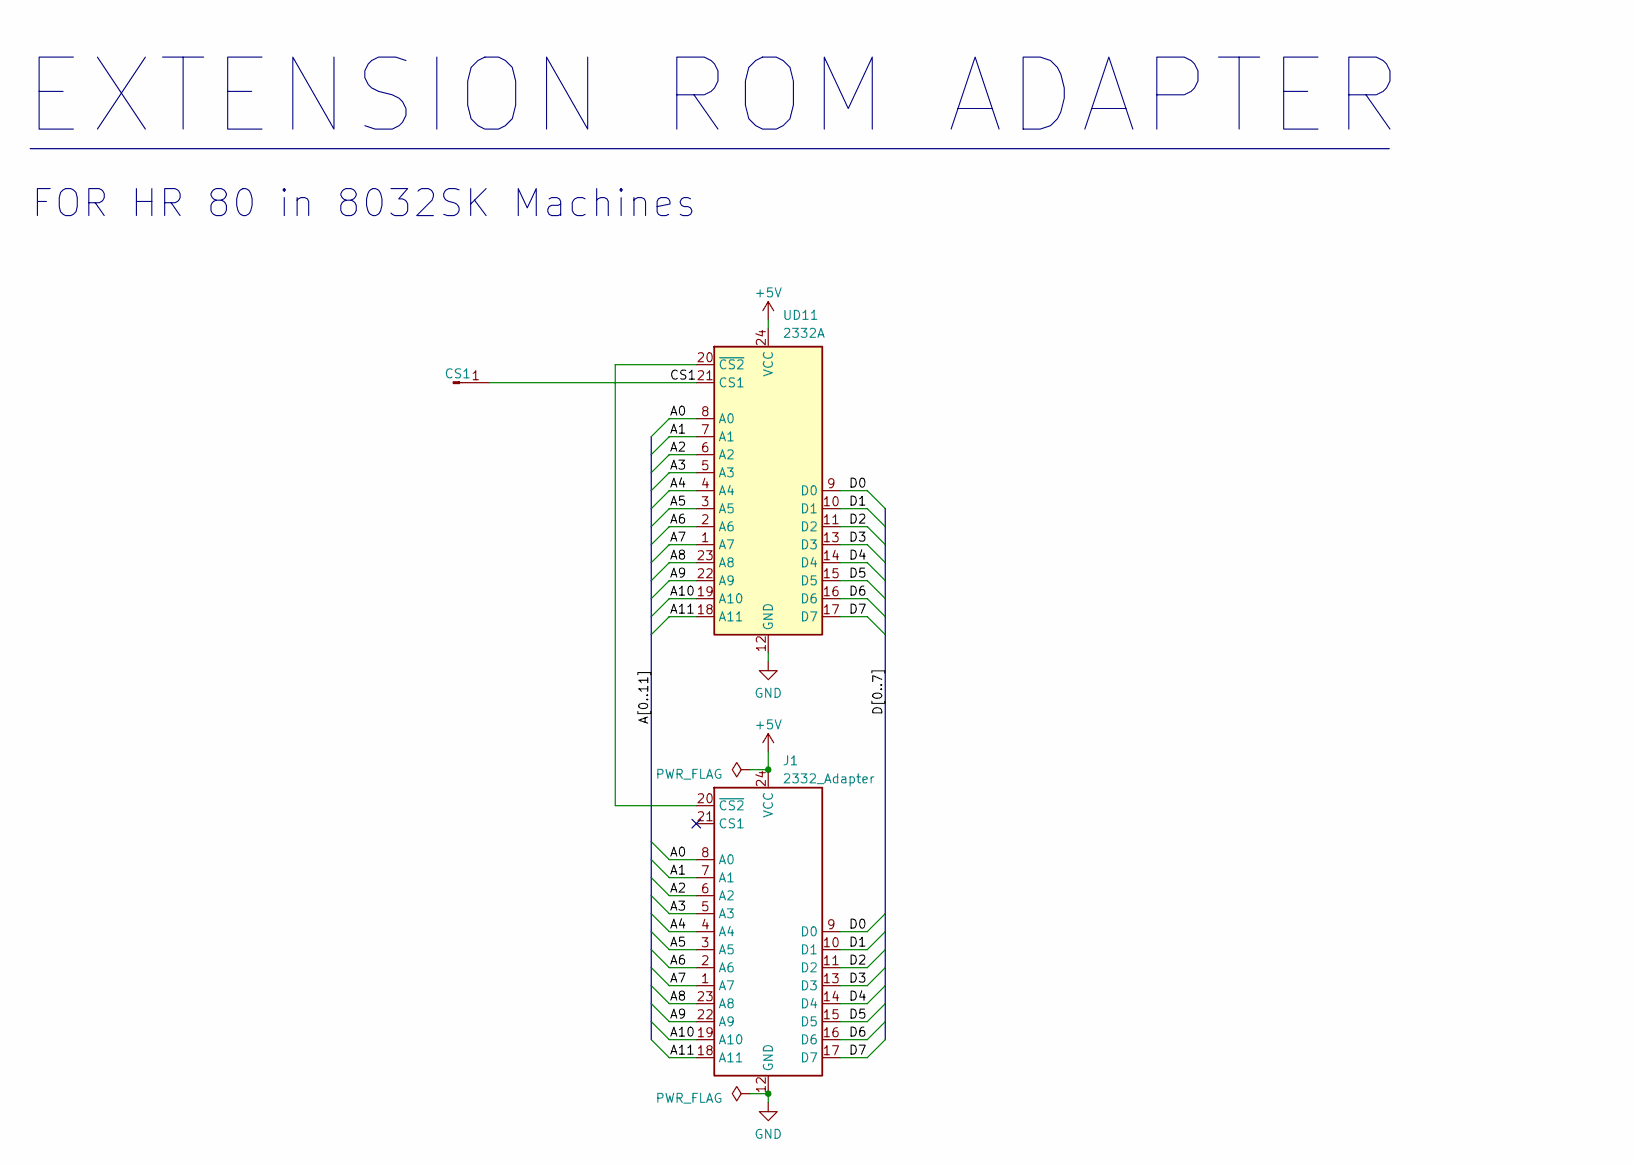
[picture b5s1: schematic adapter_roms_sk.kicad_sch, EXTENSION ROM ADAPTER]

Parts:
CS1: Conn_01x01_Pin; PinHeader_1x01_P2.54mm_Horizontal
J1: 2332_Adapter; DIP-24_W15.24mm_Adapter_Rectangularpads
UD11: 2332A; DIP-24_W15.24mm_Socket_RectangularPads

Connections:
+5V: J1.24 (VCC), UD11.24 (VCC)
/A0: J1.8 (A0), UD11.8 (A0)
/A1: J1.7 (A1), UD11.7 (A1)
/A2: J1.6 (A2), UD11.6 (A2)
/A3: J1.5 (A3), UD11.5 (A3)
/A4: J1.4 (A4), UD11.4 (A4)
/A5: J1.3 (A5), UD11.3 (A5)
/A6: J1.2 (A6), UD11.2 (A6)
/A7: J1.1 (A7), UD11.1 (A7)
/A8: J1.23 (A8), UD11.23 (A8)
/A9: J1.22 (A9), UD11.22 (A9)
/A10: J1.19 (A10), UD11.19 (A10)
/A11: J1.18 (A11), UD11.18 (A11)
/CS1: CS1.1, UD11.21 (CS1)
/D0: J1.9 (D0), UD11.9 (D0)
/D1: J1.10 (D1), UD11.10 (D1)
/D2: J1.11 (D2), UD11.11 (D2)
/D3: J1.13 (D3), UD11.13 (D3)
/D4: J1.14 (D4), UD11.14 (D4)
/D5: J1.15 (D5), UD11.15 (D5)
/D6: J1.16 (D6), UD11.16 (D6)
/D7: J1.17 (D7), UD11.17 (D7)
GND: J1.12 (GND), UD11.12 (GND)
unnamed: J1.20 (~CS2), UD11.20 (~CS2)

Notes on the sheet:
EXTENSION ROM ADAPTER
FOR HR 80 in 8032SK Machines

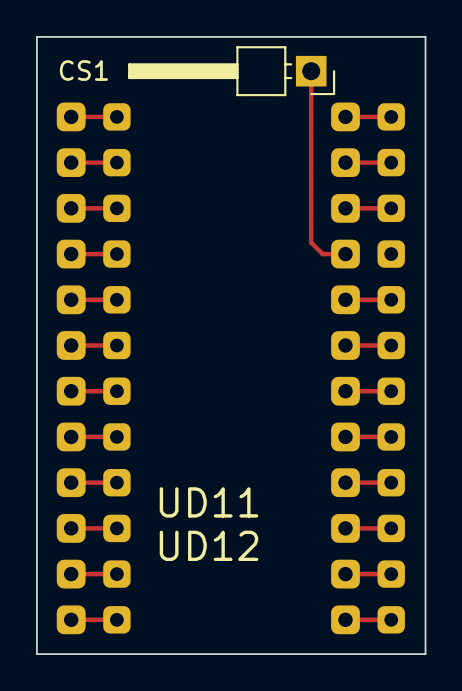
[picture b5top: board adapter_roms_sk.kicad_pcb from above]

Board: 2 copper layers, 21.6 x 34.3 mm, 3 parts (0 on the bottom side), 24 nets.

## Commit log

2024-06-24 no tented VIAs
    set the vias to be not tented in the KiCAD project to closer to the original looks
    images, BOM, gerbers adjusted to reflect that change

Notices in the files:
adapter_crtc/adapter_crtc.kicad_pcb:
License: CC BY-SA 4.0
hr40/hr40.kicad_pcb:
CC BY-SA
